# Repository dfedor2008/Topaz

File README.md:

# Topaz - A Lightweight Long-Range GPS Telemetry System

---

## What is Topaz?

Topaz is a compact, cost-effective GPS telemetry platform designed for long-range data transmission using LoRa modulation. It supports both Morse code and binary telemetry formats and integrates environmental sensing, making it suitable for high-altitude ballooning, rocket recovery, remote monitoring, and more.

---

## Features & Components

- **Microcontroller** — [ATSAMD21G18A](https://www.microchip.com/en-us/product/atsamd21g18): A reliable, low-power Cortex-M0+ MCU from Microchip.
- **LoRa Radio** — [SX1262](https://www.semtech.com/products/wireless-rf/lora-transceivers/sx1262): Sub-GHz long-range radio for Morse or telemetry data.
- **GPS Receiver** — [ATGM336H](https://jlcpcb.com/partdetail/Zhongkewei-ATGM336H5N31/C90770): Provides position and timing data.
- **Environmental Sensor** — [BME280](https://www.bosch-sensortec.com/products/environmental-sensors/humidity-sensors-bme280/): Measures temperature, humidity, and pressure.
- **Power Supply** — Designed to run from USB or external LiPo/boosted AA battery (3.3V).

---

---

## Use Cases

- Tracker for rockets
- Tracking for general uses
- Environmental monitoring (bme sensor)  

---

## How It Works

1. The **ATGM336H GPS module** gathers location and time.  
2. The **BME280** reads environmental parameters.  
3. The **SAMD21** processes the data.  
4. The **SX1262** transmits the payload via LoRa (in Morse or binary formats).  
5. A paired Topaz device or SDR can receive and decode the transmission.

All firmware is written in **C++**

---

## Hardware Setup Guide

1. **Solder the PCB** — A reflow plate is recommended for clean results.  
2. **Inspect for Shorts** — Pay extra attention around power and MCU pins.  
3. **Power Up via External Supply (not USB)** — Watch for smoke or abnormal heat. Power off immediately if detected.  
4. **Connect via USB** — Once verified safe, plug into your computer.

> After soldering and testing, upload the firmware via Arduino IDE. Topaz is optimized for affordability and robustness.

---

## PCB Diagrams

### Schematic

### Layout

---

## Software & Configuration

This project uses the Arduino platform. Libraries include:

- TinyGPS++  
- Adafruit_BME280  
- RadioHead or LoRa drivers for SX1262

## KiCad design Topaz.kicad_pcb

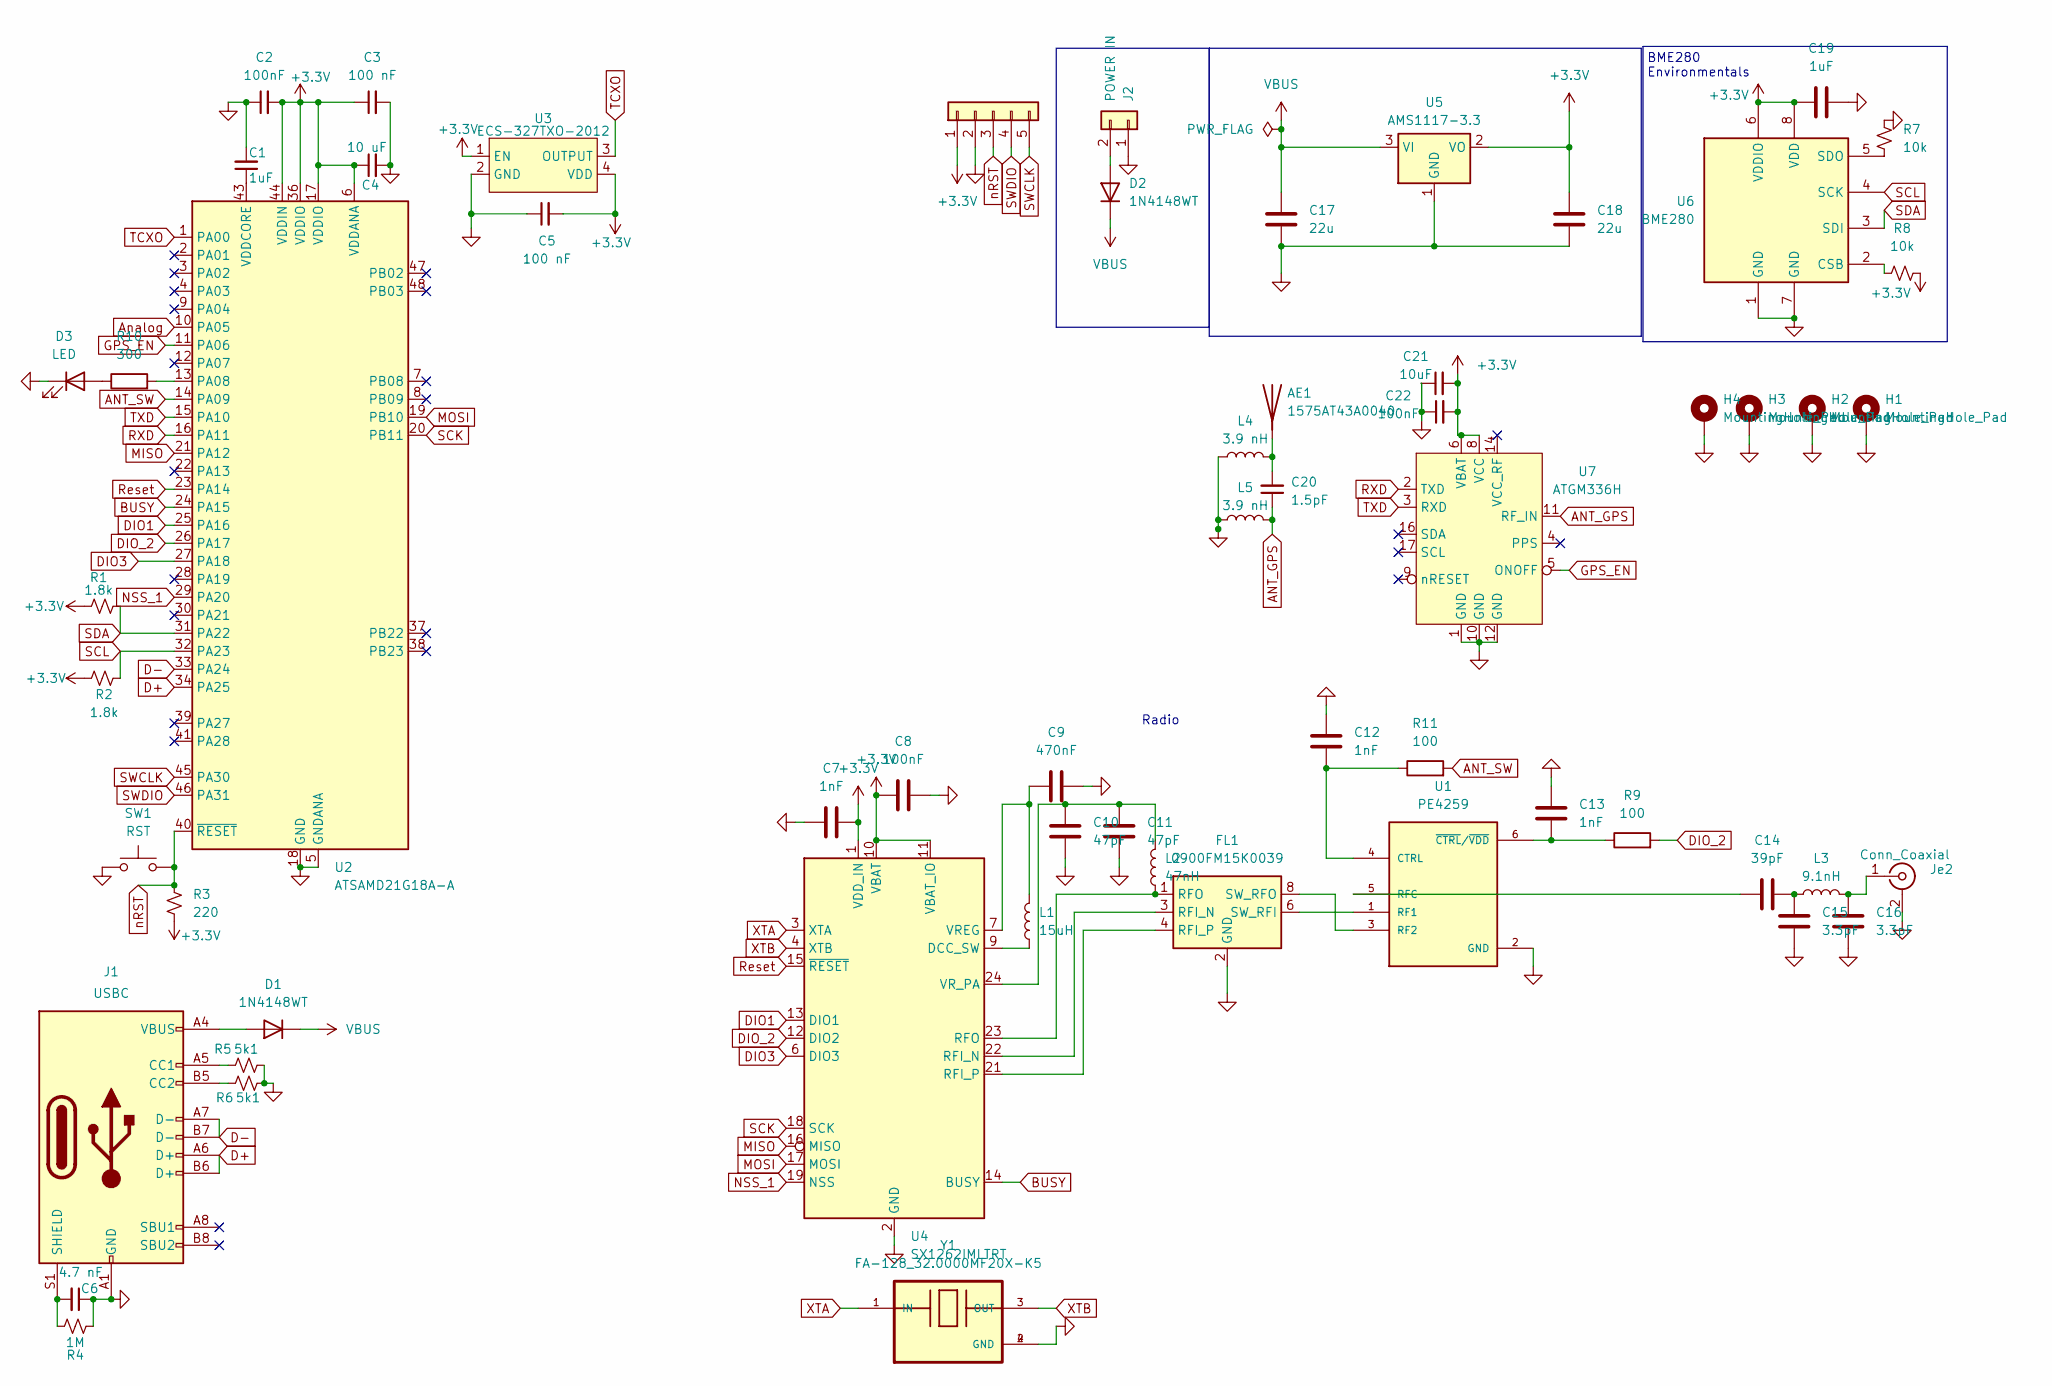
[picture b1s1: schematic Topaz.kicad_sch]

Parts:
AE1: 1575AT43A0040; 609-1575AT43A0040E; LCSC C239243
C1: 1uF; C_0402_1005Metric_Pad0.74x0.62mm_HandSolder; LCSC C52923
C2, C22: 100nF; C_0402_1005Metric_Pad0.74x0.62mm_HandSolder; LCSC C1525
C3, C5: 100 nF; C_0402_1005Metric_Pad0.74x0.62mm_HandSolder; LCSC C1525
C4: 10 uF; C_0402_1005Metric_Pad0.74x0.62mm_HandSolder; LCSC C19702
C6: 4.7 nF; C_0402_1005Metric_Pad0.74x0.62mm_HandSolder; LCSC C1744
C7, C12, C13: 1nF; C_0402_1005Metric
C8: 100nF; C_0402_1005Metric
C9: 470nF; C_0402_1005Metric
C10, C11: 47pF; C_0402_1005Metric
C14: 39pF; C_0402_1005Metric
C15, C16: 3.3pF; C_0402_1005Metric
C17, C18: 22u; C_0805_2012Metric
C19: 1uF; C_0402_1005Metric
C20: 1.5pF; C_0402_1005Metric_Pad0.74x0.62mm_HandSolder; LCSC C1525
C21: 10uF; C_0402_1005Metric_Pad0.74x0.62mm_HandSolder; LCSC C19702
D1, D2: 1N4148WT; D_SOD-523
D3: LED; LED_0402_1005Metric
FL1: 0900FM15K0039; Balun_Johanson_0900FM15K0039
H1, H2, H3, H4: MountingHole_Pad; MountingHole_2.1mm
J1: USBC; USB_C_Receptacle_GCT_USB4105-xx-A_16P_TopMnt_Horizontal; LCSC C136423
J2: POWER IN; PinHeader_1x02_P2.54mm_Vertical
J3: PinHeader_1x05_P2.54mm_Vertical
Je2: Conn_Coaxial; RFSOLUTIONS_CON-SMA-EDGE-S
L1: 15uH; L_0402_1005Metric
L2: 47nH; L_0402_1005Metric
L3: 9.1nH; L_0402_1005Metric
L4, L5: 3.9 nH; L_0402_1005Metric_Pad0.77x0.64mm_HandSolder; LCSC C307609
R1, R2: 1.8k; R_0402_1005Metric_Pad0.72x0.64mm_HandSolder; LCSC C4177
R3: 220; R_0402_1005Metric_Pad0.72x0.64mm_HandSolder; LCSC C25091
R4: 1M; R_0402_1005Metric_Pad0.72x0.64mm_HandSolder; LCSC C26083
R5, R6: 5k1; R_0402_1005Metric_Pad0.72x0.64mm_HandSolder; LCSC C27834
R7, R8: 10k; R_0402_1005Metric_Pad0.72x0.64mm_HandSolder; LCSC C25744
R9, R11: 100; R_0402_1005Metric
R10: 300; R_0402_1005Metric
SW1: RST; SW_Tactile_SPST_NO_Straight_CK_PTS636Sx25SMTRLFS; LCSC C2888954
U1: PE4259
U2: ATSAMD21G18A-A; TQFP-48_7x7mm_P0.5mm; LCSC C78624
U3: ECS-327TXO-2012; OSC_ECS-327TXO-2012-33-TR; LCSC C213398
U4: SX1262IMLTRT; QFN-24-1EP_4x4mm_P0.5mm_EP2.6x2.6mm
U5: AMS1117-3.3; SOT-223-3_TabPin2
U6: BME280; Bosch_LGA-8_2.5x2.5mm_P0.65mm_ClockwisePinNumbering
U7: ATGM336H; LCSC C5117921
Y1: FA-128_32.0000MF20X-K5; OSCCC200X160X50

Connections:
+3.3V: C2.2, C3.1, C4.1, C5.2, C7.2, C8.1, C18.1, C19.1, C21.2, C22.2, J3.1, R1.2, R2.1, R3.2, R8.1, U2.6 (VDDANA), U2.17 (VDDIO), U2.36 (VDDIO), U2.44 (VDDIN), U3.1 (EN), U3.4 (VDD), U4.1 (VDD_IN), U4.10 (VBAT), U4.11 (VBAT_IO), U5.2 (VO), U6.6 (VDDIO), U6.8 (VDD), U7.6 (VBAT), U7.8 (VCC)
ANT_GPS: C20.1, L5.2, U7.11 (RF_IN)
ANT_SW: R11.2, U2.14 (PA09)
Analog: U2.10 (PA05)
BUSY: U2.24 (PA15), U4.14 (BUSY)
D+: J1.A6 (D+), J1.B6 (D+), U2.34 (PA25)
D-: J1.A7 (D-), J1.B7 (D-), U2.33 (PA24)
DIO1: U2.25 (PA16), U4.13 (DIO1)
DIO3: U2.27 (PA18), U4.6 (DIO3)
DIO_2: R9.2, U2.26 (PA17), U4.12 (DIO2)
GND: C1.2, C2.1, C3.2, C4.2, C5.1, C6.1, C7.1, C8.2, C9.2, C10.1, C11.1, C12.1, C13.1, C15.2, C16.2, C17.2, C18.2, C19.2, C21.1, C22.1, D3.1 (K), FL1.2 (GND), FL1.5 (GND), FL1.7 (GND), FL1.9 (GND), FL1.10 (GND), H1.1, H2.1, H3.1, H4.1, J1.A1 (GND), J1.A12 (GND), J1.B1 (GND), J1.B12 (GND), J2.1, J3.2, Je2.1 (In), Je2.2 (Ext), L4.1, L5.1, R4.2, R5.1, R6.1, R7.2, SW1.1, U1.2 (GND), U2.5 (GNDANA), U2.18 (GND), U2.35 (GND), U2.42 (GND), U3.2 (GND), U4.2 (GND), U4.5 (GND), U4.8 (GND), U4.20 (GND), U4.25 (GND), U5.1 (GND), U6.1 (GND), U6.7 (GND), U7.1 (GND), U7.10 (GND), U7.12 (GND), Y1.2 (GND), Y1.4 (GND)
GPS_EN: U2.11 (PA06), U7.5 (ONOFF)
MISO: U2.21 (PA12), U4.16 (MISO)
MOSI: U2.19 (PB10), U4.17 (MOSI)
NSS_1: U2.29 (PA20), U4.19 (NSS)
unnamed: AE1.1 (A), C20.2, L4.2
unnamed: C14.2, C15.1, L3.1
unnamed: D1.2 (A), J1.A4 (VBUS), J1.A9 (VBUS), J1.B4 (VBUS), J1.B9 (VBUS)
unnamed: D2.2 (A), J2.2
unnamed: D3.2 (A), R10.1
unnamed: FL1.3 (RFI_N), U4.22 (RFI_N)
unnamed: FL1.4 (RFI_P), U4.21 (RFI_P)
unnamed: FL1.1 (RFO), L2.1, U4.23 (RFO)
unnamed: FL1.6 (SW_RFI), U1.1 (RF1)
unnamed: FL1.8 (SW_RFO), U1.3 (RF2)
unnamed: J1.A5 (CC1), R5.2
unnamed: J1.B5 (CC2), R6.2
unnamed: C6.2, J1.S1 (SHIELD), R4.1
unnamed: C16.1, Je2.1 (In), L3.2
unnamed: C12.2, R11.1, U1.4 (CTRL)
unnamed: C14.1, U1.5 (RFC)
unnamed: C13.2, R9.1, U1.6 (~CTRL/~VDD)
unnamed: R10.2, U2.13 (PA08)
unnamed: C1.1, U2.43 (VDDCORE)
unnamed: L1.1, U4.9 (DCC_SW)
unnamed: C9.1, L1.2, U4.7 (VREG)
unnamed: C10.2, C11.2, L2.2, U4.24 (VR_PA)
unnamed: R8.2, U6.2 (CSB)
unnamed: R7.1, U6.5 (SDO)
RXD: U2.16 (PA11), U7.2 (TXD)
Reset: U2.23 (PA14), U4.15 (~RESET)
SCK: U2.20 (PB11), U4.18 (SCK)
SCL: R2.2, U2.32 (PA23), U6.4 (SCK)
SDA: R1.1, U2.31 (PA22), U6.3 (SDI)
SWCLK: J3.5, U2.45 (PA30)
SWDIO: J3.4, U2.46 (PA31)
TCXO: U2.1 (PA00), U3.3 (OUTPUT)
TXD: U2.15 (PA10), U7.3 (RXD)
VBUS: C17.1, D1.1 (K), D2.1 (K), U5.3 (VI)
XTA: U4.3 (XTA), Y1.1 (IN)
XTB: U4.4 (XTB), Y1.3 (OUT)
nRST: J3.3, R3.1, SW1.2, U2.40 (~RESET)

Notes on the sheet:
BME280 Environmentals
Radio

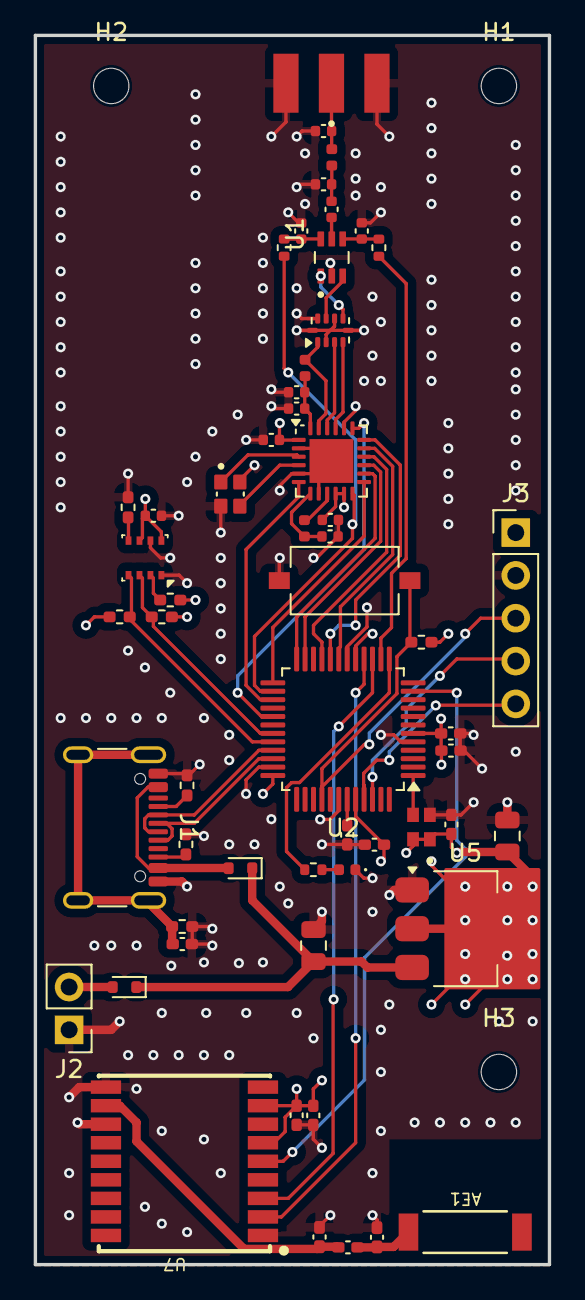
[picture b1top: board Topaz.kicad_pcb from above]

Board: 4 copper layers, 30.5 x 72.9 mm, 60 parts (0 on the bottom side), 51 nets.

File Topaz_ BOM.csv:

"null","Sourced","Placed","References","Value","Footprint","Quantity"
1,"✓","✓","C7, C12, C13","1nF","C_0402_1005Metric",3
2,"✓","✓","C2, C22","100nF","C_0402_1005Metric_Pad0.74x0.62mm_HandSolder",2
3,"","","C3, C5","100 nF","C_0402_1005Metric_Pad0.74x0.62mm_HandSolder",2
4,"✓","✓","C10, C11","47pF","C_0402_1005Metric",2
5,"","","C15, C16","3.3pF","C_0402_1005Metric",2
6,"✓","✓","C17, C18","22u","C_0805_2012Metric",2
7,"","","C1","1uF","C_0402_1005Metric_Pad0.74x0.62mm_HandSolder",1
8,"","","C4","10 uF","C_0402_1005Metric_Pad0.74x0.62mm_HandSolder",1
9,"✓","✓","C6","4.7 nF","C_0402_1005Metric_Pad0.74x0.62mm_HandSolder",1
10,"","","C8","100nF","C_0402_1005Metric",1
11,"✓","✓","C9","470nF","C_0402_1005Metric",1
12,"✓","✓","C14","39pF","C_0402_1005Metric",1
13,"✓","✓","C19","1uF","C_0402_1005Metric",1
14,"✓","✓","C20","1.5pF","C_0402_1005Metric_Pad0.74x0.62mm_HandSolder",1
15,"✓","✓","C21","10uF","C_0402_1005Metric_Pad0.74x0.62mm_HandSolder",1
16,"✓","✓","R1, R2","1.8k","R_0402_1005Metric_Pad0.72x0.64mm_HandSolder",2
17,"✓","✓","R5, R6","5k1","R_0402_1005Metric_Pad0.72x0.64mm_HandSolder",2
18,"","","R7, R8","10k","R_0402_1005Metric_Pad0.72x0.64mm_HandSolder",2
19,"✓","✓","R9, R11",100,"R_0402_1005Metric",2
20,"✓","✓","R3",220,"R_0402_1005Metric_Pad0.72x0.64mm_HandSolder",1
21,"","","R4","1M","R_0402_1005Metric_Pad0.72x0.64mm_HandSolder",1
22,"✓","✓","R10",300,"R_0402_1005Metric",1
23,"✓","✓","L4, L5","3.9 nH","L_0402_1005Metric_Pad0.77x0.64mm_HandSolder",2
24,"✓","✓","L1","15uH","L_0402_1005Metric",1
25,"✓","✓","L2","47nH","L_0402_1005Metric",1
26,"✓","✓","L3","9.1nH","L_0402_1005Metric",1
27,"","","D1, D2","1N4148WT","D_SOD-523",2
28,"✓","✓","D3","LED","LED_0402_1005Metric",1
29,"✓","✓","U1","PE4259","PE4259",1
30,"✓","✓","U2","ATSAMD21G18A-A","TQFP-48_7x7mm_P0.5mm",1
31,"✓","✓","U3","ECS-327TXO-2012","OSC_ECS-327TXO-2012-33-TR",1
32,"✓","✓","U4","SX1262IMLTRT","QFN-24-1EP_4x4mm_P0.5mm_EP2.6x2.6mm",1
33,"","","U5","AMS1117-3.3","SOT-223-3_TabPin2",1
34,"✓","✓","U6","BME280","Bosch_LGA-8_2.5x2.5mm_P0.65mm_ClockwisePinNumbering",1
35,"✓","✓","U7","ATGM336H","ATGM336H",1
36,"✓","✓","Y1","FA-128_32.0000MF20X-K5","OSCCC200X160X50",1
37,"✓","✓","SW1","RST","SW_Tactile_SPST_NO_Straight_CK_PTS636Sx25SMTRLFS",1
38,"✓","✓","AE1","1575AT43A0040","609-1575AT43A0040E",1
39,"✓","✓","FL1","0900FM15K0039","Balun_Johanson_0900FM15K0039",1
40,"✓","✓","Je2","Conn_Coaxial","RFSOLUTIONS_CON-SMA-EDGE-S",1
41,"✓","✓","J1","USBC","USB_C_Receptacle_GCT_USB4105-xx-A_16P_TopMnt_Horizontal",1
42,"","","J2","POWER IN","PinHeader_1x02_P2.54mm_Vertical",1
43,"✓","✓","J3","~","PinHeader_1x05_P2.54mm_Vertical",1

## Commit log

2025-05-31 Rename Topaz.csv to Topaz_BOM.csv
2025-06-08 Gerber files
2025-06-11 Rename Topaz (2).csv to Topaz_ BOM.csv
2025-06-11 Rename Untitled.png to 3D_Image.png
